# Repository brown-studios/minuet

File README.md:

# Minuet fan controller

Minuet upgrades your [MAXXAIR Maxxfan](https://www.maxxair.com/products/fans/maxxfan-deluxe/) with a brushless DC motor, home automation features, and accessories.

Improve your quality of life in your campervan, RV, trailer, or truck!

* Replace your fan's original motor with a quieter brushless motor. No more cleaning squeaky motor brushes!
* Install Minuet with simple hand tools. You can revert back to the original equipment later if you want.
* Connect your fan to your home automation system if you have one. Works with your original infrared remote control and wired wall controls too.
* Install the light accessory to add a ring of lights to your fan for illumination and ambiance.
* Install the environmental sensor accessory to measure CO₂, temperature, humidity, and barometric pressure and automatically provide ventilation when it gets stuffy inside.
* Install the cover sensor accessory to stop the fan and turn off the lights automatically when you attach an insulated vent cover.
* Enjoy a more polished user experience with enhanced controls, more automation, and less beeping.
* Customize your fan as you like because the firmware and hardware are open source!
  * Expand the [ESPHome](https://esphome.io/)-based [firmware](https://github.com/brown-studios/minuet-firmware).
  * Connect off-the-shelf I2C environmental sensors and devices to the [QWIIC](https://www.sparkfun.com/qwiic) port.
  * Make your own hardware accessories for the expansion port.
  * Share your work with the community!

This repository contains the Minuet documentation and hardware design files.  You are welcome to modify the Minuet firmware and hardware subject to the [license terms](#notice) and we encourage you to make your own accessories.  We welcome thoughtful contributions.

*Refer to the [Minuet firmware repository](https://github.com/brown-studios/minuet-firmware) for source code.*

## Get to know Minuet

Watch Minuet in action and follow along with how it was made with these videos:

* [Minuet showcase](https://vimeo.com/showcase/11857354)
* [Minuet build log](https://vimeo.com/showcase/11858950)

## Project status

Minuet is in active development.

The latest prototype is feature complete, works well, and is being tested by a few volunteers.

Our next tasks are finalizing the design, working with manufacturers to fabricate kits with everything you will need to upgrade your Maxxfan, and planning for order fulfillment.  We are also investigating the possibility of manufacturing custom brushless fan motors that will fit into the fan housing with fewer adapters.  Please contact us if you would like to contribute your manufacturing experience to this project.

Watch this space for updates on our progress.  We're thrilled by your interest in Minuet and we look forward to offering you a great upgrade for your Maxxfan!

See [project history](./docs/project-history.md) for the story of how we got here.

## Author's note

Hey folks, I'm Jeff!

I started building my campervan in 2023 after some delightful adventures in New Zealand.  Like many of you, I installed a Maxxfan in my campervan because it was the most popular fan for van builders.  It worked well for a while but less than a year after I installed it, the fan started making some awful squeaking noises.  I tried the usual advice: clean the motor brushes, replace the bearings, run the motor on high for a day, and nothing helped for long.  I tried to ignore the problem.

When the winter rainy season arrived and interrupted my van build, I started the squeaking fan again.  I had already started designing a circuit board to synchronize the Maxxfan with my home automation system and I found it tedious to work around the existing logic of the Maxxfan circuit board.  It occurred to me that it might be easier to design my own controller from scratch... and then I could use a brushless fan motor and solve my fan squeaking problem too!

So here we are.  I've made several prototypes, enjoyed the quiet, added quality of life features, made some friends, and learned a lot along the way.  I'm satisfied with how Minuet has improved my comfort and I hope you'll like it too.

## Getting started

Read these guides to learn how to build, install, and use Minuet and its accessories.

1. [Hardware guide](docs/hardware-guide.md): How to build Minuet hardware.
1. [Installation guide](docs/installation-guide.md): How to install Minuet into your Maxxfan.
1. [User guide](docs/user-guide.md): How to use Minuet.

Good luck and enjoy your fan!

## Compatibility

Minuet is anticipated to be *compatible* with the following Maxxfan models.  Some models have yet to be specifically tested and are shown as unverified in the table.

| Compatible model | Lid type | Lid color | Temperature sensor | Rain sensor | Infrared receiver | Verified |
| ---------------- | -------- | --------- | ------------------ | ----------- | ----------------- | -------- |
| Maxxfan Deluxe 7500K | rain cover | smoke | yes | no | yes | yes |
| Maxxfan Deluxe 7000K | rain cover | white | yes | no | yes | no |
| Maxxfan Deluxe 6200K | rain cover | smoke | yes | no | no † | no |
| Maxxfan Deluxe 5100K | rain cover | white | yes | no | no † | no |
| Maxxfan Plus 4500K‡ | low profile | smoke | yes | yes | yes | yes |

†: When you install Minuet in a Maxxfan whose keypad does not have a window for an infrared receiver, you will be unable to use Minuet's infrared remote control features. (It may be possible to replace or punch a hole through the keypad to make a window for the infrared receiver and use its features.)

‡: The Maxxfan Plus 4500K lid takes longer to open and close so the firmware must be modified to account for the extra duration as of Minuet v3.0.  This difference will be resolved by improving end-of-travel detection.

Minuet is *not compatible* with the following Maxxfan models.

| Incompatible models | Reason |
| ------------------- | ------ |
| Maxxfan Deluxe 5101K, 6201K, 7001K, 7501K, 8001K, 8501K | exhaust only keypad (no in/out button) |
| Maxxfan Deluxe 5301K, 6401K | 4 speed keypad (different buttons) |
| Maxxfan Plus 4000K, 4002K, 4050K | manual lift |
| Maxxfan 4301K, 4401K, 4501K | manual lift |
| Maxxfan Low Profile, Mini, Dome | different electronics |

## Contributing

We welcome thoughtful contributions to this project made without the use of generative AI / LLM tools.

## Notice

The Minuet software, documentation, design, and all copyright protected artifacts are released under the terms of the [MIT license](LICENSE).

The Minuet hardware is released under the terms of the [CERN-OHL-W license](hardware/LICENSE).

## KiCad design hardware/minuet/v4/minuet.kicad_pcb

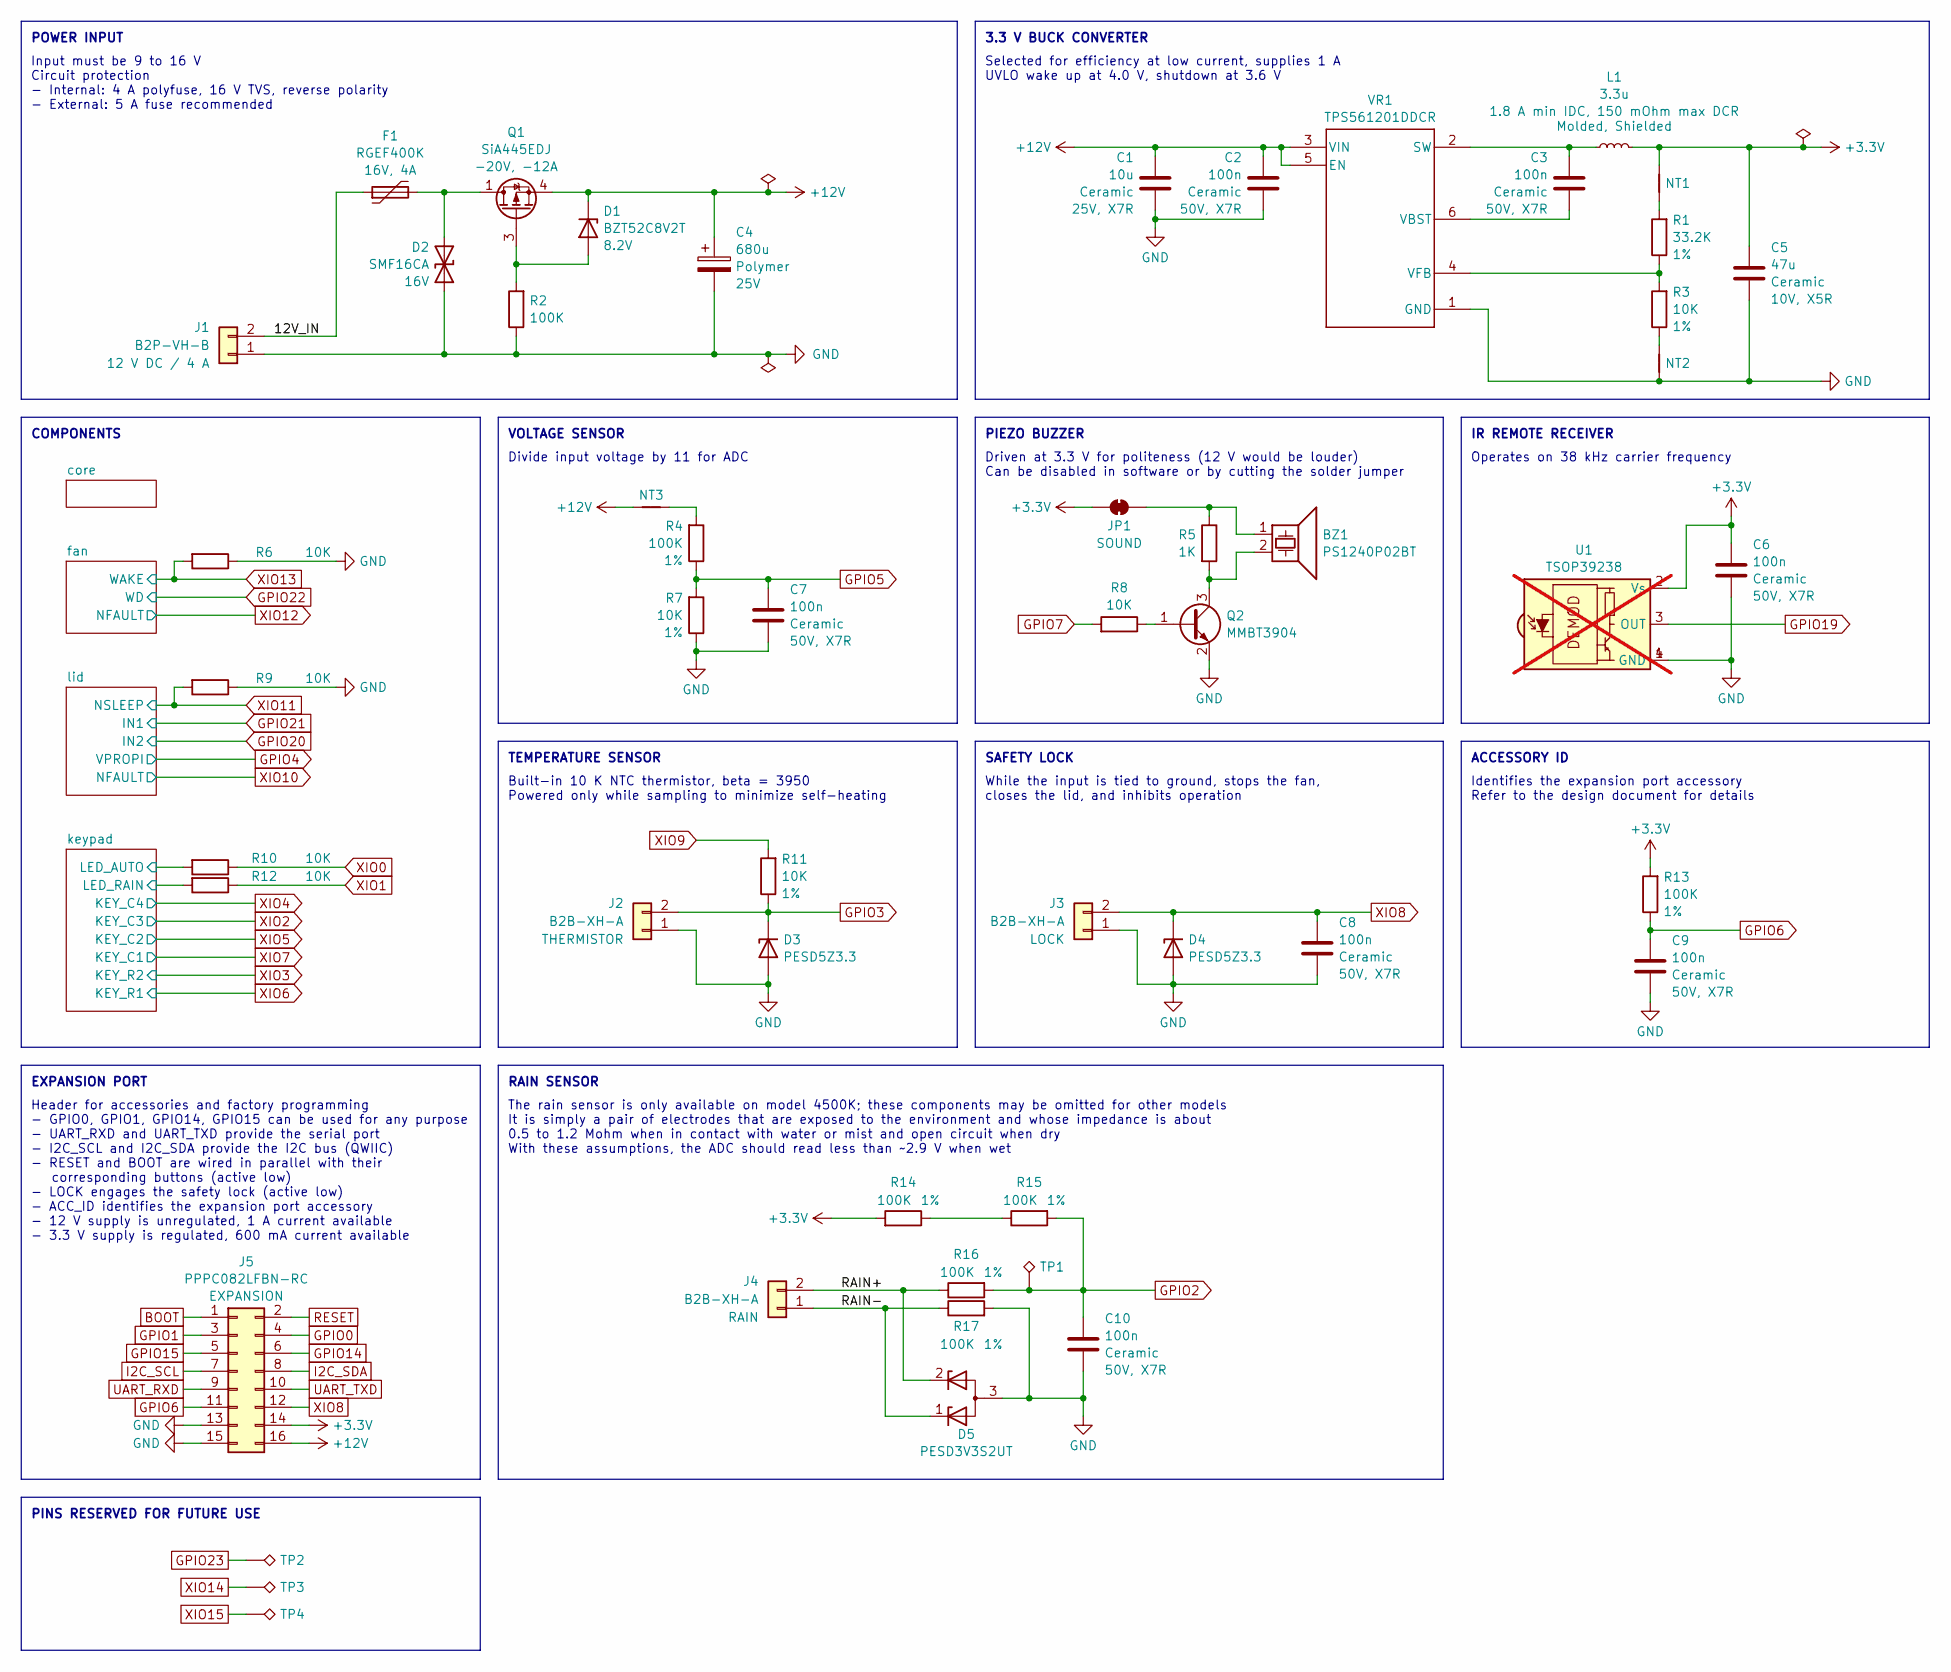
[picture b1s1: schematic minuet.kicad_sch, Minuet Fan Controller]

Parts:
BZ1: PS1240P02BT; Buzzer_TDK_PS1240P02BT_D12.2mm_H6.5mm; LCSC C76871
C1: 10u; C_1210_3225Metric; Rating 25V, X7R; Part CL32B106KAJNNNE; LCSC C39232
C2, C3, C6, C7, C8, C9, C10: 100n; C_0603_1608Metric; Rating 50V, X7R; LCSC C14663
C4: 680u; CP_Radial_D8.0mm_P3.50mm; Rating 25V; LCSC C5243855
C5: 47u; C_1206_3216Metric; Rating 10V, X5R; LCSC C96123
D1: BZT52C8V2T; D_SOD-523; Rating 8.2V; LCSC C5125761
D2: SMF16CA; D_SMF; Rating 16V; LCSC C1851354
D3, D4: PESD5Z3.3; D_SOD-523; LCSC C182940
D5: PESD3V3S2UT; SOT-23; LCSC C84276
F1: RGEF400K; Rating 16V, 4A; LCSC C135392
J1: B2P-VH-B; JST_VH_B2P-VH-B_1x02_P3.96mm_Vertical; LCSC C265114
J2, J3, J4: B2B-XH-A; JST_XH_B2B-XH-A_1x02_P2.50mm_Vertical; LCSC C158012
J5: PPPC082LFBN-RC; PinSocket_2x08_P2.54mm_Vertical; LCSC C30734
JP1: SolderJumper_2_Bridged; SolderJumper-2_P1.3mm_Bridged_RoundedPad1.0x1.5mm
L1: 3.3u; L_1008_2520Metric; Rating 1.8 A min IDC, 150 mOhm max DCR; Part AOTA-B252010S3R3MT; LCSC C22416628
NT1, NT2, NT3: NetTie_2; NetTie-2_SMD_Pad0.2mm
Q1: SiA445EDJ; Vishay_PowerPAK_SC70-6L_Single; Rating -20V, -12A; LCSC C144959
Q2: MMBT3904; SOT-23; LCSC C20526
R1: 33.2K; R_0603_1608Metric; Rating 1%; LCSC C4216
R2, R4, R13, R14, R15, R16, R17: 100K; R_0603_1608Metric; Rating 1%; LCSC C25803
R3, R6, R7, R8, R9, R10, R11, R12: 10K; R_0603_1608Metric; Rating 1%; LCSC C25804
R5: 1K; R_0603_1608Metric; Rating 1%; LCSC C21190
TP1, TP2, TP3, TP4: TestPoint_Alt; TestPoint_Pad_D1.0mm
U1: TSOP39238; TSOP39238_Standoff; LCSC C7128407; not fitted
VR1: TPS561201DDCR; SOT95P280X110-6N; LCSC C220433

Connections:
+3.3V: C5.1, C6.1, J5.14, JP1.1 (A), L1.1, NT1.2, R13.2, R14.2, U1.2 (Vs); also elsewhere on the board
+12V: C1.1, C2.1, C4.1, D1.1 (K), J5.16, NT3.1, Q1.4 (S), VR1.3 (VIN), VR1.5 (EN); also elsewhere on the board
/12V_IN: F1.1, J1.2
/RAIN+: D5.2 (K), J4.2, R16.1
/RAIN-: D5.1 (K), J4.1, R17.1
/keypad/LED_AUTO: R10.2; also elsewhere on the board
/keypad/LED_RAIN: R12.2; also elsewhere on the board
BOOT: J5.1; also elsewhere on the board
GND: C1.2, C2.2, C4.2, C5.2, C6.2, C7.2, C8.2, C9.2, C10.2, D2.1 (A1), D3.2 (A), D4.2 (A), D5.3 (A), J1.1, J2.1, J3.1, J5.13, J5.15, NT2.1, Q2.2 (E), R2.1, R6.1, R7.1, R9.1, R17.2, U1.1 (GND), U1.4 (GND), VR1.1 (GND); also elsewhere on the board
GPIO0: J5.4; also elsewhere on the board
GPIO1: J5.3; also elsewhere on the board
GPIO2: C10.1, R15.2, R16.2, TP1.1; also elsewhere on the board
GPIO3: D3.1 (K), J2.2, R11.1; also elsewhere on the board
GPIO5: C7.1, R4.1, R7.2; also elsewhere on the board
GPIO6: C9.1, J5.11, R13.1; also elsewhere on the board
GPIO7: R8.2; also elsewhere on the board
GPIO14: J5.6; also elsewhere on the board
GPIO15: J5.5; also elsewhere on the board
GPIO19: U1.3 (OUT); also elsewhere on the board
GPIO23: TP2.1; also elsewhere on the board
I2C_SCL: J5.7; also elsewhere on the board
I2C_SDA: J5.8; also elsewhere on the board
unnamed: D1.2 (A), Q1.3 (G), R2.2
unnamed: D2.2 (A2), F1.2, Q1.1 (D)
unnamed: BZ1.1, JP1.2 (B), R5.1
unnamed: NT1.1, R1.2
unnamed: NT2.2, R3.1
unnamed: NT3.2, R4.2
unnamed: Q2.1 (B), R8.1
unnamed: BZ1.2, Q2.3 (C), R5.2
unnamed: R14.1, R15.1
unnamed: C3.1, L1.2, VR1.2 (SW)
unnamed: C3.2, VR1.6 (VBST)
unnamed: R1.1, R3.2, VR1.4 (VFB)
RESET: J5.2; also elsewhere on the board
UART_RXD: J5.9; also elsewhere on the board
UART_TXD: J5.10; also elsewhere on the board
XIO0: R10.1; also elsewhere on the board
XIO1: R12.1; also elsewhere on the board
XIO8: C8.1, D4.1 (K), J3.2, J5.12; also elsewhere on the board
XIO9: R11.2; also elsewhere on the board
XIO11: R9.2; also elsewhere on the board
XIO13: R6.2; also elsewhere on the board
XIO14: TP3.1; also elsewhere on the board
XIO15: TP4.1; also elsewhere on the board

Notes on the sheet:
ACCESSORY ID
RAIN SENSOR
VOLTAGE SENSOR
Driven at 3.3 V for politeness (12 V would be louder) Can be disabled in software or by cutting the solder jumper
POWER INPUT
Identifies the expansion port accessory Refer to the design document for details
3.3 V BUCK CONVERTER
EXPANSION PORT
Operates on 38 kHz carrier frequency
The rain sensor is only available on model 4500K; these components may be omitted for other models It is simply a pair of electrodes that are exposed to the environment and whose impedance is about 0.5 to 1.2 Mohm when in contact with water or mist and open circuit when dry With these assumptions, 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
Input must be 9 to 16 V Circuit protection - Internal: 4 A polyfuse, 16 V TVS, reverse polarity - External: 5 A fuse recommended
Header for accessories and factory programming - GPIO0, GPIO1, GPIO14, GPIO15 can be used for any purpose - UART_RXD and UART_TXD provide the serial port - I2C_SCL and I2C_SDA provide the I2C bus (QWIIC) - RESET and BOOT are wired in parallel with their corresponding buttons (active low) - LOCK eng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
While the input is tied to ground, stops the fan, closes the lid, and inhibits operation
PINS RESERVED FOR FUTURE USE
IR REMOTE RECEIVER
PIEZO BUZZER
Selected for efficiency at low current, supplies 1 A UVLO wake up at 4.0 V, shutdown at 3.6 V
TEMPERATURE SENSOR
Divide input voltage by 11 for ADC
Built-in 10 K NTC thermistor, beta = 3950 Powered only while sampling to minimize self-heating
SAFETY LOCK
COMPONENTS

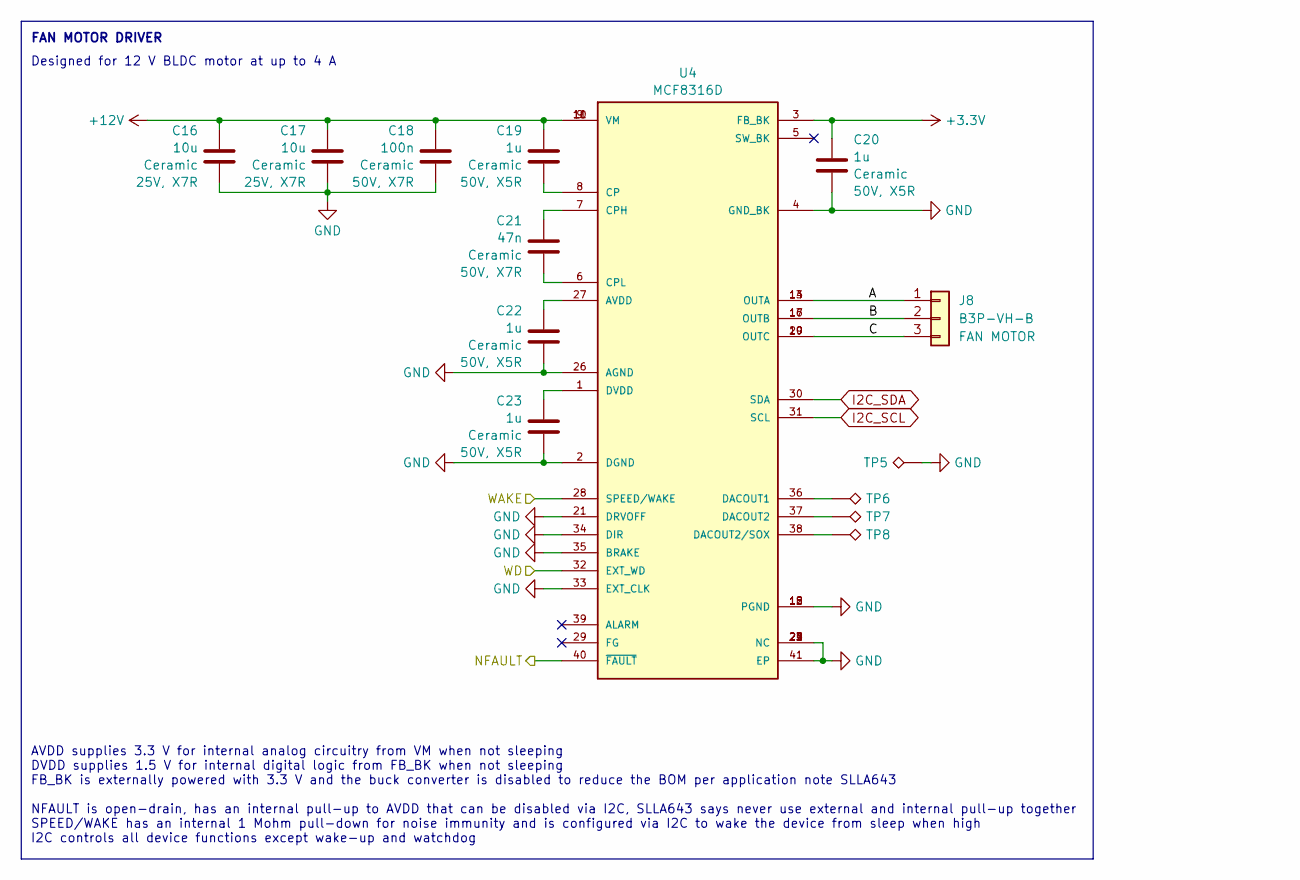
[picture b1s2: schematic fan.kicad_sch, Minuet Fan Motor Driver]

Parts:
C16, C17: 10u; C_1210_3225Metric; Rating 25V, X7R; Part CL32B106KAJNNNE; LCSC C39232
C18: 100n; C_0603_1608Metric; Rating 50V, X7R; LCSC C14663
C19, C20, C22, C23: 1u; C_0603_1608Metric; Rating 50V, X5R; LCSC C15849
C21: 47n; C_0603_1608Metric; Rating 50V, X7R; LCSC C1622
J8: B3P-VH-B; JST_VH_B3P-VH-B_1x03_P3.96mm_Vertical; LCSC C265360
TP5, TP6, TP7, TP8: TestPoint_Alt; TestPoint_Pad_D1.0mm
U4: MCF8316D; LCSC C42453588

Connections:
+3.3V: C20.1, U4.3 (FB_BK); also elsewhere on the board
+12V: C16.1, C17.1, C18.1, C19.1, U4.9 (VM), U4.10 (VM), U4.11 (VM); also elsewhere on the board
/fan/A: J8.1, U4.13 (OUTA), U4.14 (OUTA)
/fan/B: J8.2, U4.16 (OUTB), U4.17 (OUTB)
/fan/C: J8.3, U4.19 (OUTC), U4.20 (OUTC)
GND: C16.2, C17.2, C18.2, C20.2, C22.2, C23.2, TP5.1, U4.2 (DGND), U4.4 (GND_BK), U4.12 (PGND), U4.15 (PGND), U4.18 (PGND), U4.21 (DRVOFF), U4.22 (NC), U4.23 (NC), U4.24 (NC), U4.25 (NC), U4.26 (AGND), U4.33 (EXT_CLK), U4.34 (DIR), U4.35 (BRAKE), U4.41 (EP); also elsewhere on the board
GPIO22: U4.32 (EXT_WD); also elsewhere on the board
I2C_SCL: U4.31 (SCL); also elsewhere on the board
I2C_SDA: U4.30 (SDA); also elsewhere on the board
unnamed: C22.1, U4.27 (AVDD)
unnamed: C19.2, U4.8 (CP)
unnamed: C21.1, U4.7 (CPH)
unnamed: C21.2, U4.6 (CPL)
unnamed: TP6.1, U4.36 (DACOUT1)
unnamed: TP7.1, U4.37 (DACOUT2)
unnamed: TP8.1, U4.38 (DACOUT2/SOX)
unnamed: C23.1, U4.1 (DVDD)
XIO12: U4.40 (~FAULT); also elsewhere on the board
XIO13: U4.28 (SPEED/WAKE); also elsewhere on the board

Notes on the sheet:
FAN MOTOR DRIVER
Designed for 12 V BLDC motor at up to 4 A
AVDD supplies 3.3 V for internal analog circuitry from VM when not sleeping DVDD supplies 1.5 V for internal digital logic from FB_BK when not sleeping FB_BK is externally powered with 3.3 V and the buck converter is disabled to reduce the BOM per application note SLLA643 NFAULT is open-drain, has 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

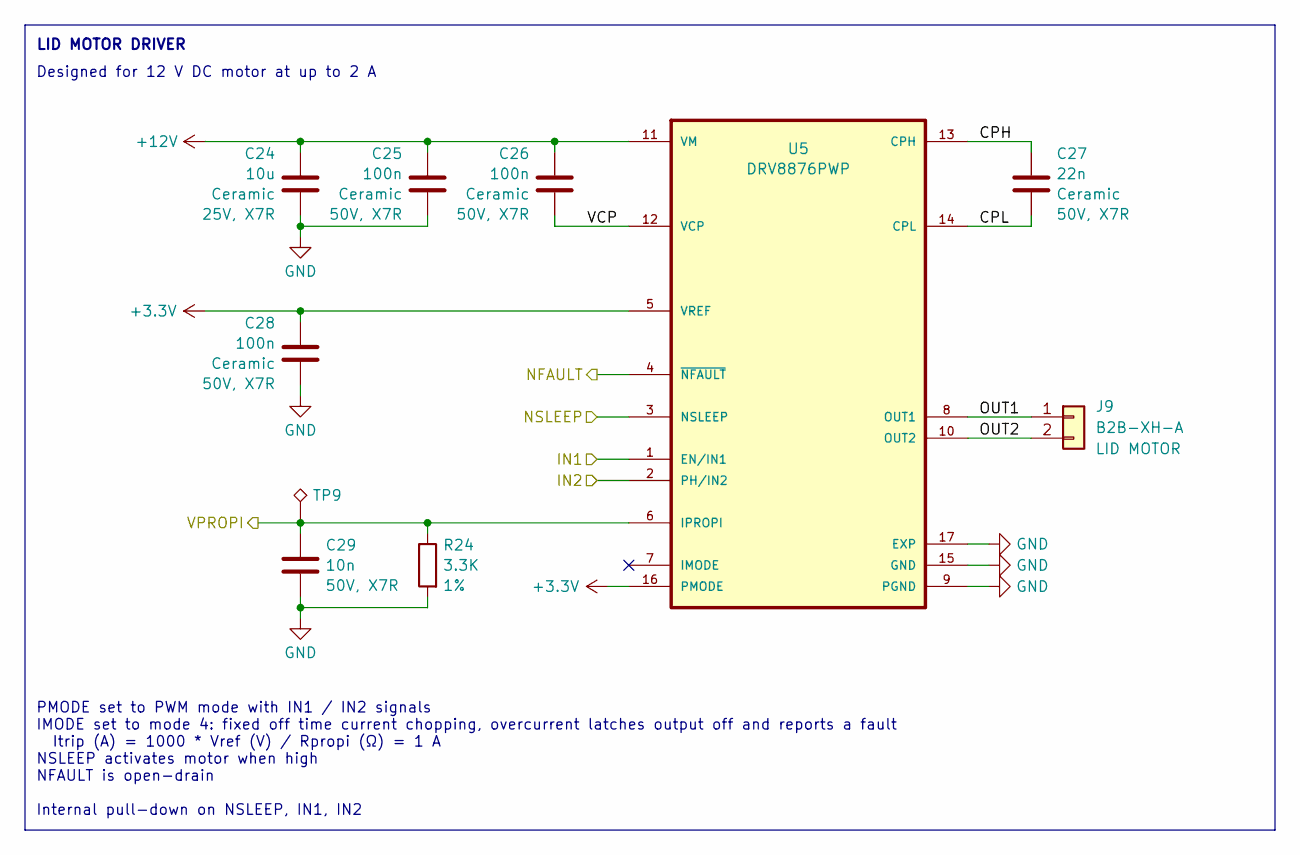
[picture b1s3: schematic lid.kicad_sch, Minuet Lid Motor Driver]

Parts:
C24: 10u; C_1210_3225Metric; Rating 25V, X7R; Part CL32B106KAJNNNE; LCSC C39232
C25, C26, C28: 100n; C_0603_1608Metric; Rating 50V, X7R; LCSC C14663
C27: 22n; C_0603_1608Metric; Rating 50V, X7R; LCSC C21122
C29: 10n; C_0603_1608Metric; Rating 50V, X7R; LCSC C57112
J9: B2B-XH-A; JST_XH_B2B-XH-A_1x02_P2.50mm_Vertical; LCSC C158012
R24: 3.3K; R_0603_1608Metric; Rating 1%; LCSC C22978
TP9: TestPoint_Alt; TestPoint_Pad_D1.0mm
U5: DRV8876PWP; IC_DRV8876PWPR; PARTREV E; LCSC C575551

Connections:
+3.3V: C28.1, U5.5 (VREF), U5.16 (PMODE); also elsewhere on the board
+12V: C24.1, C25.1, C26.1, U5.11 (VM); also elsewhere on the board
/lid/CPH: C27.1, U5.13 (CPH)
/lid/CPL: C27.2, U5.14 (CPL)
/lid/OUT1: J9.1, U5.8 (OUT1)
/lid/OUT2: J9.2, U5.10 (OUT2)
/lid/VCP: C26.2, U5.12 (VCP)
GND: C24.2, C25.2, C28.2, C29.2, R24.2, U5.9 (PGND), U5.15 (GND), U5.17 (EXP); also elsewhere on the board
GPIO4: C29.1, R24.1, TP9.1, U5.6 (IPROPI); also elsewhere on the board
GPIO20: U5.2 (PH/IN2); also elsewhere on the board
GPIO21: U5.1 (EN/IN1); also elsewhere on the board
XIO10: U5.4 (~NFAULT); also elsewhere on the board
XIO11: U5.3 (NSLEEP); also elsewhere on the board

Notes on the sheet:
PMODE set to PWM mode with IN1 / IN2 signals IMODE set to mode 4: fixed off time current chopping, overcurrent latches output off and reports a fault Itrip (A) = 1000 * Vref (V) / Rpropi (Ω) = 1 A NSLEEP activates motor when high NFAULT is open-drain Internal pull-down on NSLEEP, IN1, IN2
Designed for 12 V DC motor at up to 2 A
LID MOTOR DRIVER

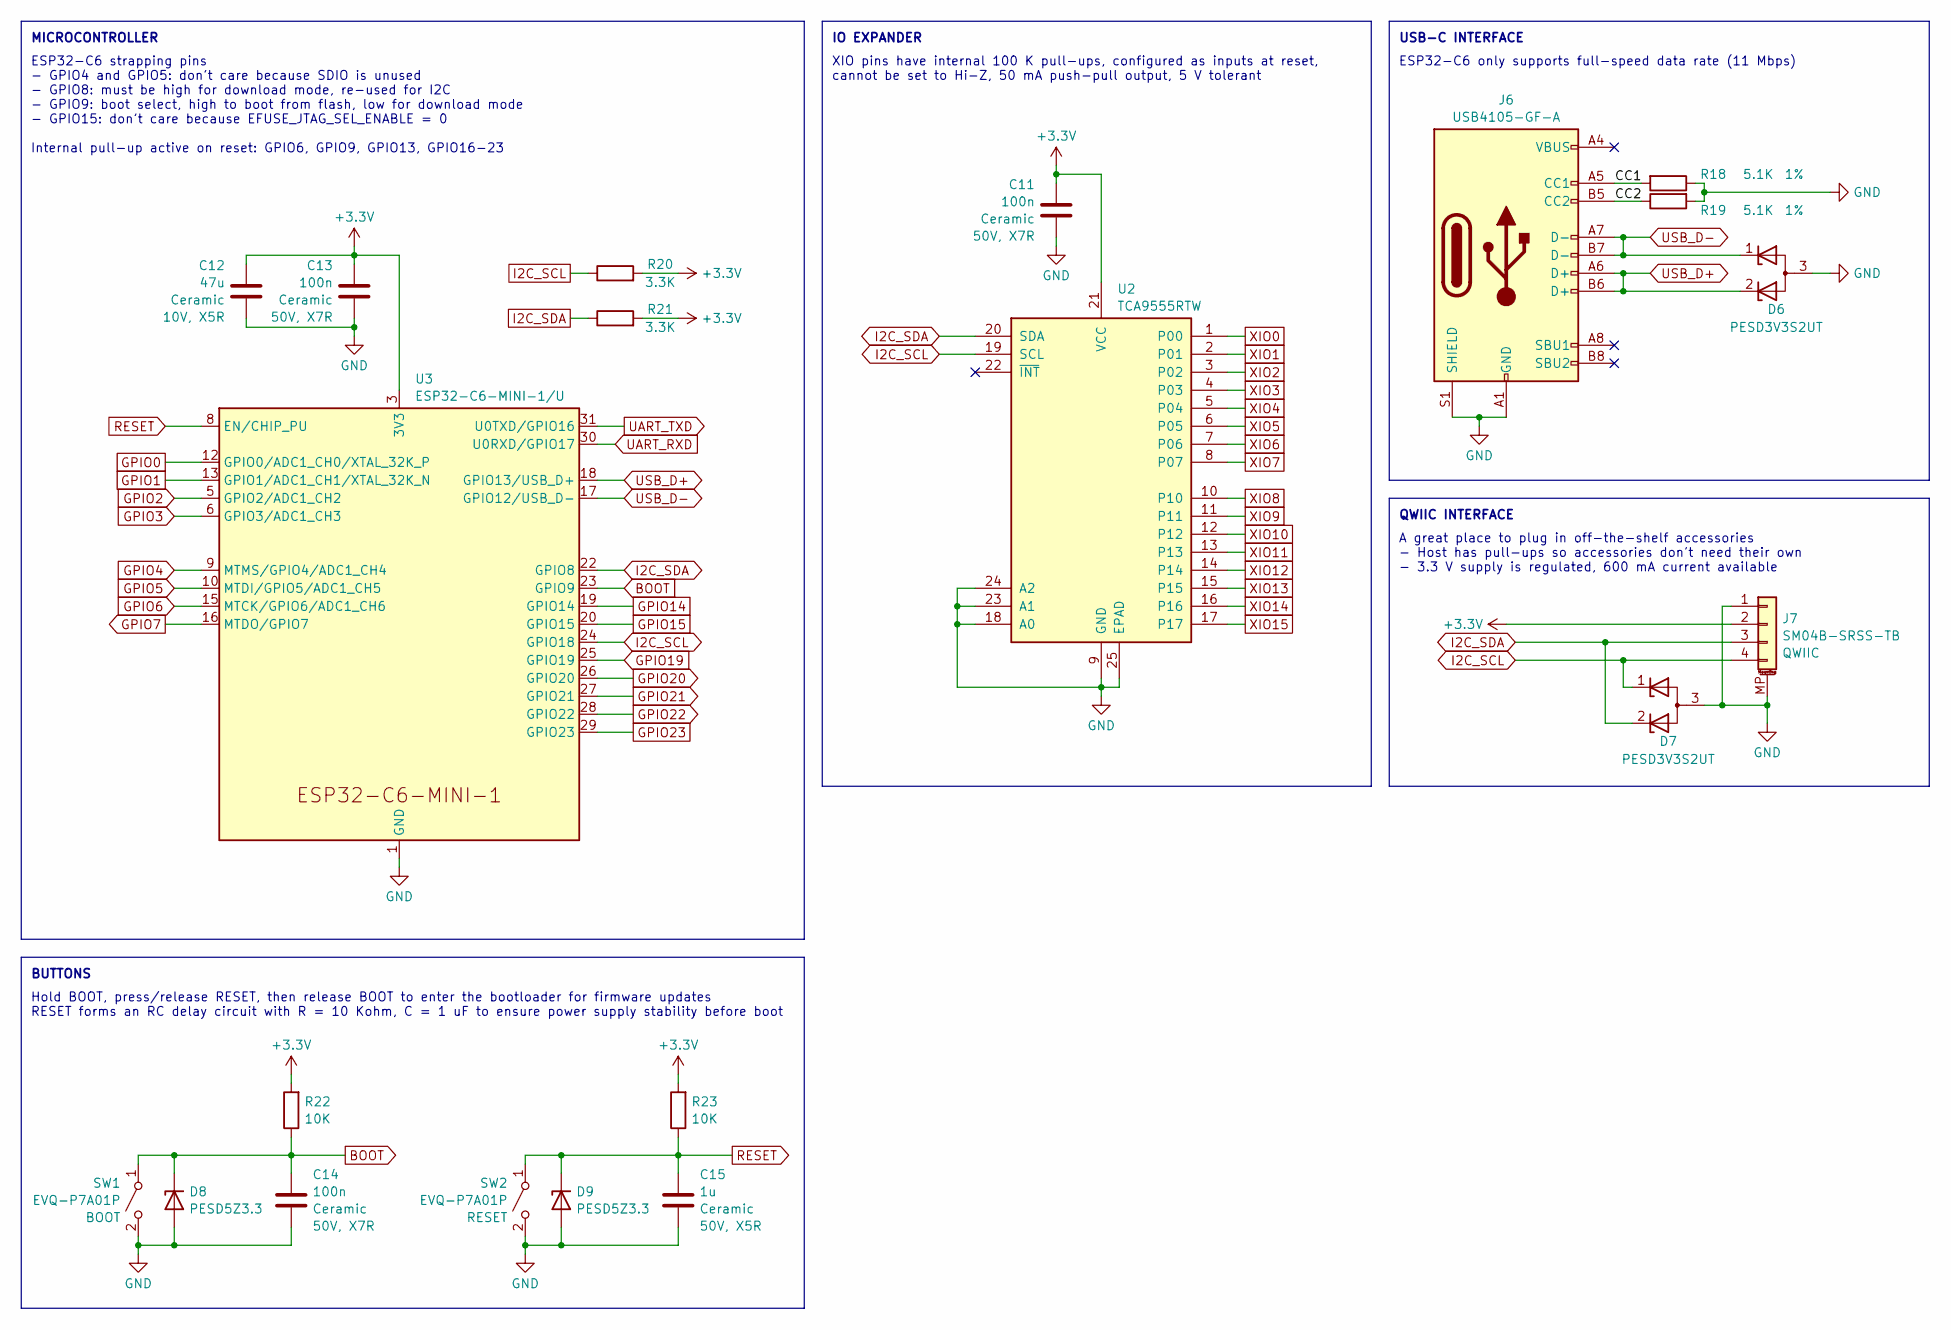
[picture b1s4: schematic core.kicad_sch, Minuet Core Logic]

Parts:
C11, C13, C14: 100n; C_0603_1608Metric; Rating 50V, X7R; LCSC C14663
C12: 47u; C_1206_3216Metric; Rating 10V, X5R; LCSC C96123
C15: 1u; C_0603_1608Metric; Rating 50V, X5R; LCSC C15849
D6, D7: PESD3V3S2UT; SOT-23; LCSC C84276
D8, D9: PESD5Z3.3; D_SOD-523; LCSC C182940
J6: USB4105-GF-A; USB_C_Receptacle_GCT_USB4105-xx-A_16P_TopMnt_Horizontal; LCSC C2988369
J7: SM04B-SRSS-TB; JST_SH_SM04B-SRSS-TB_1x04-1MP_P1.00mm_Horizontal; LCSC C160404
R18, R19: 5.1K; R_0603_1608Metric; Rating 1%; LCSC C23186
R20, R21: 3.3K; R_0603_1608Metric; Rating 1%; LCSC C22978
R22, R23: 10K; R_0603_1608Metric; Rating 1%; LCSC C25804
SW1, SW2: EVQ-P7A01P; SW_SPST_EVQP7A; LCSC C79167
U2: TCA9555RTW; WQFN-24-1EP_4x4mm_P0.5mm_EP2.45x2.45mm; LCSC C140277
U3: ESP32-C6-MINI-1/U; ESP32-C6-MINI-1; LCSC C5736265

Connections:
+3.3V: C11.1, C12.1, C13.1, J7.2, R20.2, R21.2, R22.2, R23.2, U2.21 (VCC), U3.3 (3V3); also elsewhere on the board
/core/CC1: J6.A5 (CC1), R18.2
/core/CC2: J6.B5 (CC2), R19.1
BOOT: C14.1, D8.1 (K), R22.1, SW1.1 (A), U3.23 (GPIO9); also elsewhere on the board
GND: C11.2, C12.2, C13.2, C14.2, C15.2, D6.3 (A), D7.3 (A), D8.2 (A), D9.2 (A), J6.A1 (GND), J6.A12 (GND), J6.B1 (GND), J6.B12 (GND), J6.S1 (SHIELD), J7.1, J7.MP (MountPin), R18.1, R19.2, SW1.2 (B), SW2.2 (B), U2.9 (GND), U2.18 (A0), U2.23 (A1), U2.24 (A2), U2.25 (EPAD), U3.1 (GND), U3.2 (GND), U3.11 (GND), U3.14 (GND), U3.36 (GND), U3.37 (GND), U3.38 (GND), U3.39 (GND), U3.40 (GND), U3.41 (GND), U3.42 (GND), U3.43 (GND), U3.44 (GND), U3.45 (GND), U3.46 (GND), U3.47 (GND), U3.48 (GND), U3.49 (GND), U3.50 (GND), U3.51 (GND), U3.52 (GND), U3.53 (GND); also elsewhere on the board
GPIO0: U3.12 (GPIO0/ADC1_CH0/XTAL_32K_P); also elsewhere on the board
GPIO1: U3.13 (GPIO1/ADC1_CH1/XTAL_32K_N); also elsewhere on the board
GPIO2: U3.5 (GPIO2/ADC1_CH2); also elsewhere on the board
GPIO3: U3.6 (GPIO3/ADC1_CH3); also elsewhere on the board
GPIO4: U3.9 (MTMS/GPIO4/ADC1_CH4); also elsewhere on the board
GPIO5: U3.10 (MTDI/GPIO5/ADC1_CH5); also elsewhere on the board
GPIO6: U3.15 (MTCK/GPIO6/ADC1_CH6); also elsewhere on the board
GPIO7: U3.16 (MTDO/GPIO7); also elsewhere on the board
GPIO14: U3.19 (GPIO14); also elsewhere on the board
GPIO15: U3.20 (GPIO15); also elsewhere on the board
GPIO19: U3.25 (GPIO19); also elsewhere on the board
GPIO20: U3.26 (GPIO20); also elsewhere on the board
GPIO21: U3.27 (GPIO21); also elsewhere on the board
GPIO22: U3.28 (GPIO22); also elsewhere on the board
GPIO23: U3.29 (GPIO23); also elsewhere on the board
I2C_SCL: D7.1 (K), J7.4, R20.1, U2.19 (SCL), U3.24 (GPIO18); also elsewhere on the board
I2C_SDA: D7.2 (K), J7.3, R21.1, U2.20 (SDA), U3.22 (GPIO8); also elsewhere on the board
RESET: C15.1, D9.1 (K), R23.1, SW2.1 (A), U3.8 (EN/CHIP_PU); also elsewhere on the board
UART_RXD: U3.30 (U0RXD/GPIO17); also elsewhere on the board
UART_TXD: U3.31 (U0TXD/GPIO16); also elsewhere on the board
USB_D+: D6.2 (K), J6.A6 (D+), J6.B6 (D+), U3.18 (GPIO13/USB_D+)
USB_D-: D6.1 (K), J6.A7 (D-), J6.B7 (D-), U3.17 (GPIO12/USB_D-)
XIO0: U2.1 (P00); also elsewhere on the board
XIO1: U2.2 (P01); also elsewhere on the board
XIO2: U2.3 (P02); also elsewhere on the board
XIO3: U2.4 (P03); also elsewhere on the board
XIO4: U2.5 (P04); also elsewhere on the board
XIO5: U2.6 (P05); also elsewhere on the board
XIO6: U2.7 (P06); also elsewhere on the board
XIO7: U2.8 (P07); also elsewhere on the board
XIO8: U2.10; also elsewhere on the board
XIO9: U2.11; also elsewhere on the board
XIO10: U2.12; also elsewhere on the board
XIO11: U2.13; also elsewhere on the board
XIO12: U2.14; also elsewhere on the board
XIO13: U2.15; also elsewhere on the board
XIO14: U2.16; also elsewhere on the board
XIO15: U2.17; also elsewhere on the board

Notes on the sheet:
IO EXPANDER
USB-C INTERFACE
XIO pins have internal 100 K pull-ups, configured as inputs at reset, cannot be set to Hi-Z, 50 mA push-pull output, 5 V tolerant
ESP32-C6 strapping pins - GPIO4 and GPIO5: don't care because SDIO is unused - GPIO8: must be high for download mode, re-used for I2C - GPIO9: boot select, high to boot from flash, low for download mode - GPIO15: don't care because EFUSE_JTAG_SEL_ENABLE = 0 Internal pull-up active on reset: GPIO6, 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
Hold BOOT, press/release RESET, then release BOOT to enter the bootloader for firmware updates RESET forms an RC delay circuit with R = 10 Kohm, C = 1 uF to ensure power supply stability before boot
BUTTONS
ESP32-C6 only supports full-speed data rate (11 Mbps)
QWIIC INTERFACE
A great place to plug in off-the-shelf accessories - Host has pull-ups so accessories don't need their own - 3.3 V supply is regulated, 600 mA current available
MICROCONTROLLER

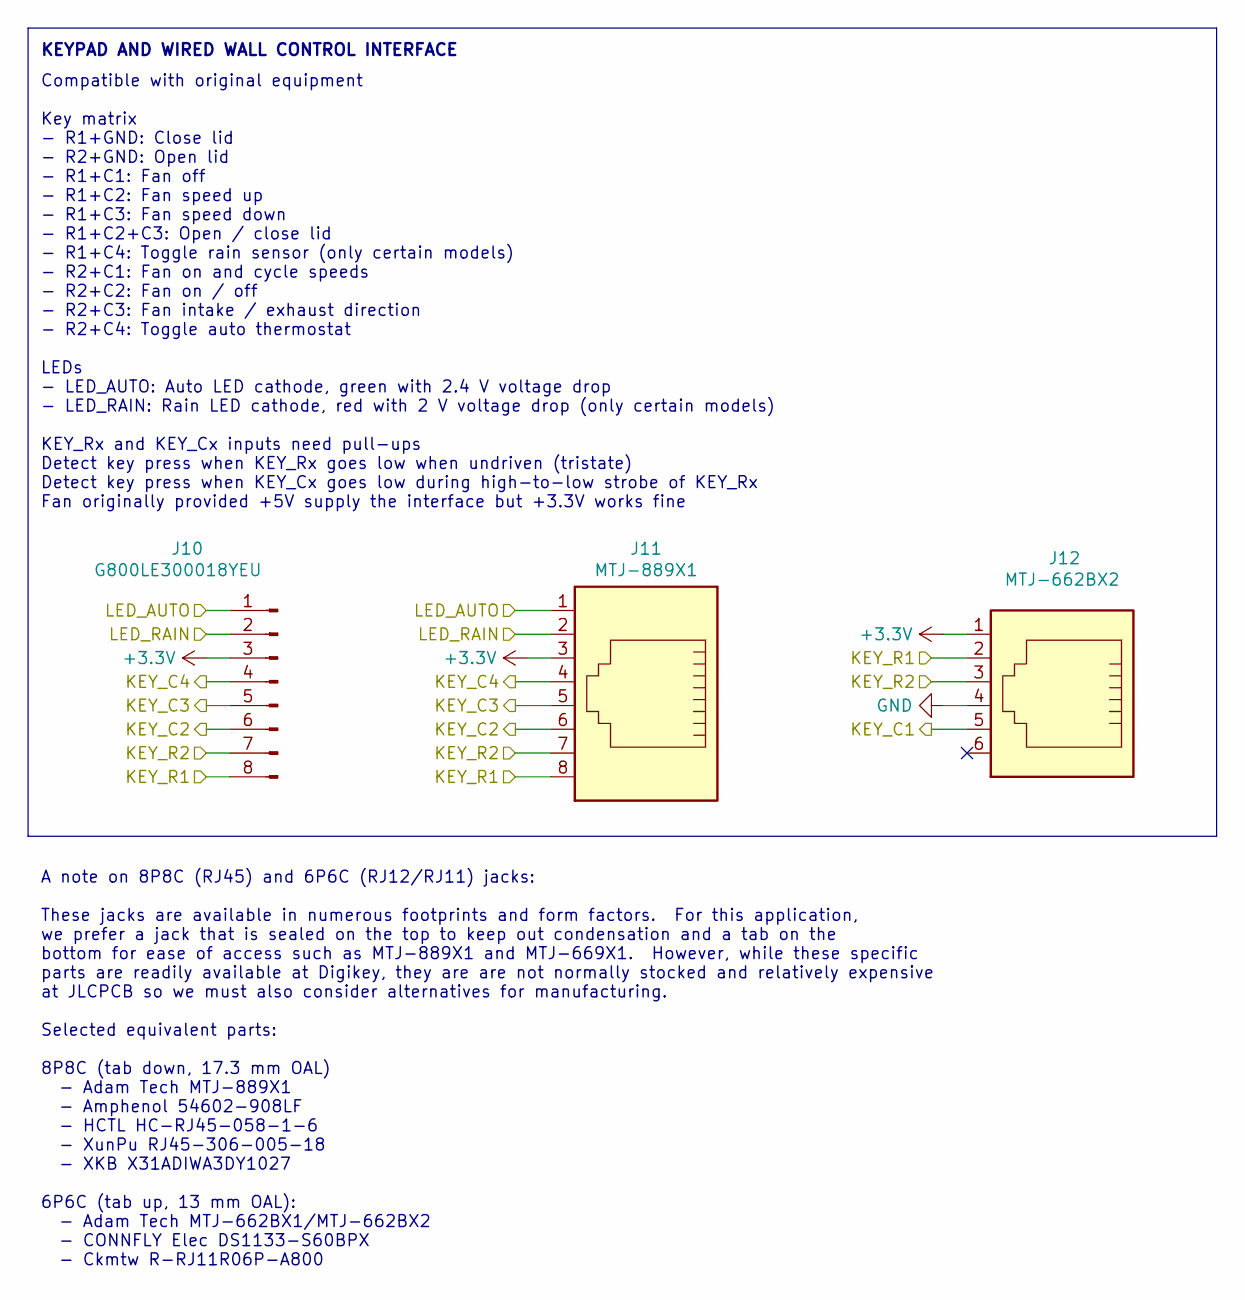
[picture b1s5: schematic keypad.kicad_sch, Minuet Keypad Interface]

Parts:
J10: G800LE300018YEU; PinHeader_1x08_P2.54mm_Vertical; LCSC_Preferred C3345591
J11: MTJ-889X1; LCSC C3000197
J12: MTJ-662BX2; LCSC C77859

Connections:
+3.3V: J10.3, J11.3, J12.1; also elsewhere on the board
/keypad/LED_AUTO: J10.1, J11.1; also elsewhere on the board
/keypad/LED_RAIN: J10.2, J11.2; also elsewhere on the board
GND: J12.4; also elsewhere on the board
XIO2: J10.5, J11.5; also elsewhere on the board
XIO3: J10.7, J11.7, J12.3; also elsewhere on the board
XIO4: J10.4, J11.4; also elsewhere on the board
XIO5: J10.6, J11.6; also elsewhere on the board
XIO6: J10.8, J11.8, J12.2; also elsewhere on the board
XIO7: J12.5; also elsewhere on the board

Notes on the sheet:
A note on 8P8C (RJ45) and 6P6C (RJ12/RJ11) jacks: These jacks are available in numerous footprints and form factors. For this application, we prefer a jack that is sealed on the top to keep out condensation and a tab on the bottom for ease of access such as MTJ-889X1 and MTJ-669X1. However, while t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
Compatible with original equipment Key matrix - R1+GND: Close lid - R2+GND: Open lid - R1+C1: Fan off - R1+C2: Fan speed up - R1+C3: Fan speed down - R1+C2+C3: Open / close lid - R1+C4: Toggle rain sensor (only certain models) - R2+C1: Fan on and cycle speeds - R2+C2: Fan on / off - R2+C3: Fan inta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
KEYPAD AND WIRED WALL CONTROL INTERFACE
